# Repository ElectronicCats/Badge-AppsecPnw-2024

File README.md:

# Badge pnwCON 2024

## Getting started

1. Connect Badge via USB to your computer.
2. Open the serial port indicated for the badge on your computer through a program such as Arduino IDE, Putty or Screen at 115200 bauds.
3. The badge text should appear in the terminal.

## Tecnologia

- ESP32C6
- LEDs
- USB

## Gratitude
Do you want to say thank you? Tag these companies on social networks and show them your badge, thanks to them it is possible

- [WebSEC](https://www.websec.ca)
- [ElectronicCats](https://electroniccats.com/)

## License

Electronic Cats invests time and resources providing this open source design, please support Electronic Cats and open-source hardware by purchasing products from Electronic Cats!

Designed by Electronic Cats.

Hardware released under an CERN Open Hardware Licence v1.2. See the LICENSE_HARDWARE file for more information.

Electronic Cats is a registered trademark, please do not use if you sell these PCBs.

May 2024

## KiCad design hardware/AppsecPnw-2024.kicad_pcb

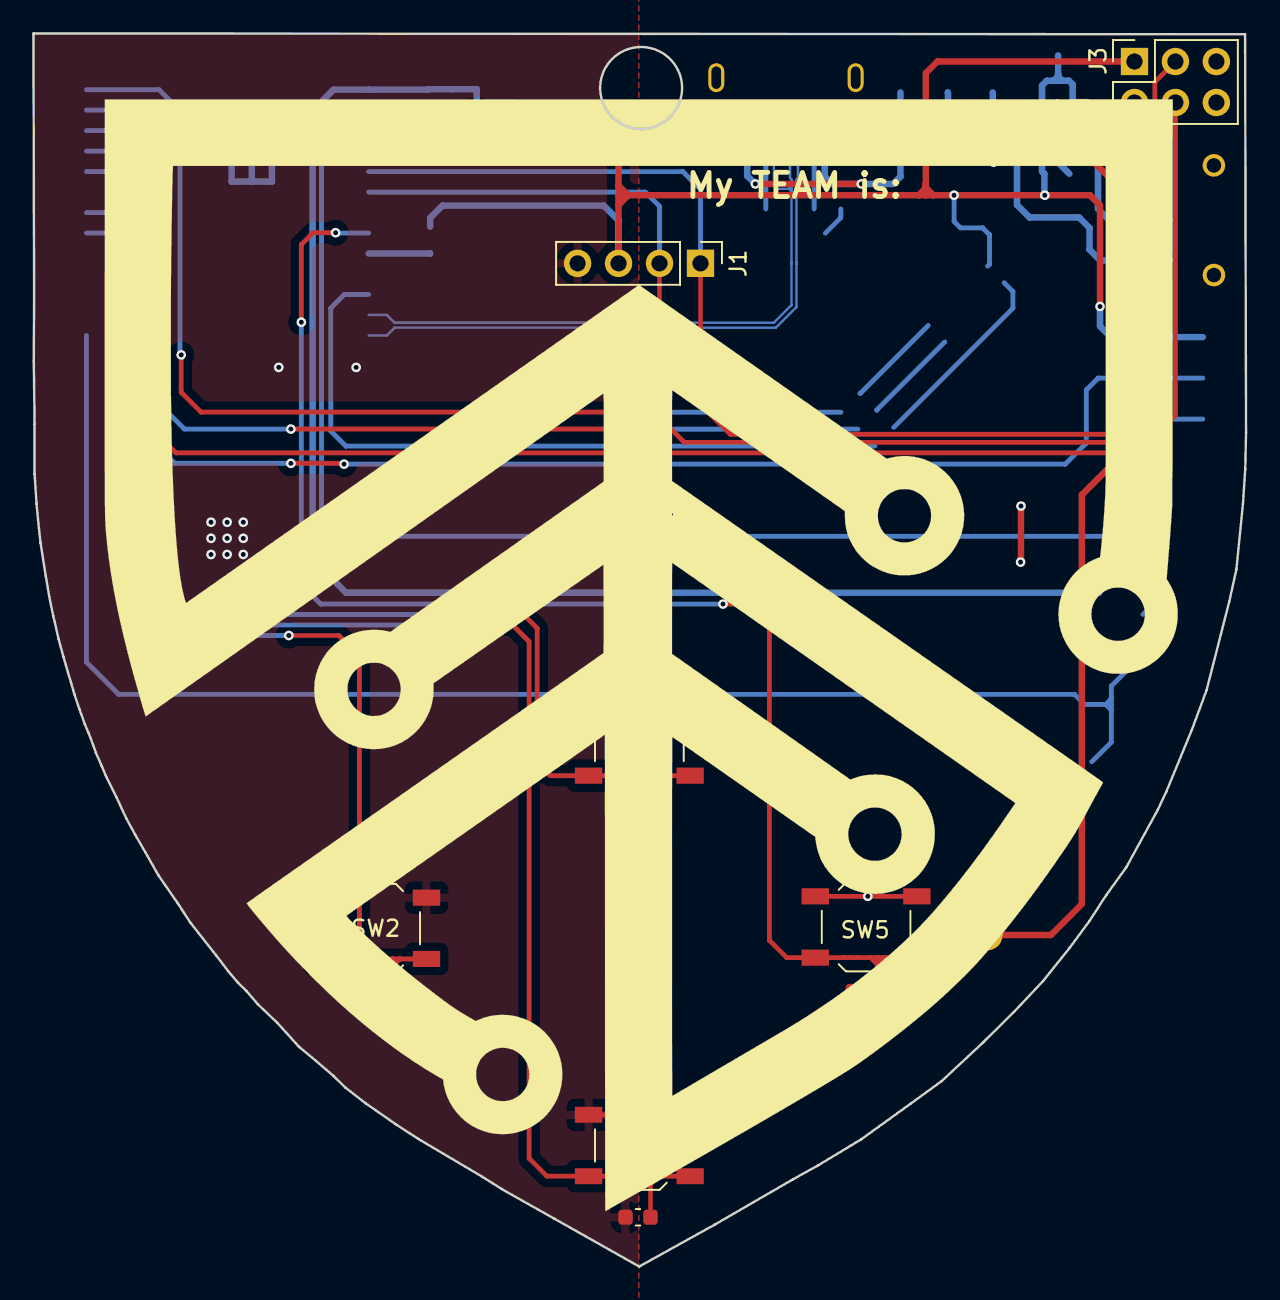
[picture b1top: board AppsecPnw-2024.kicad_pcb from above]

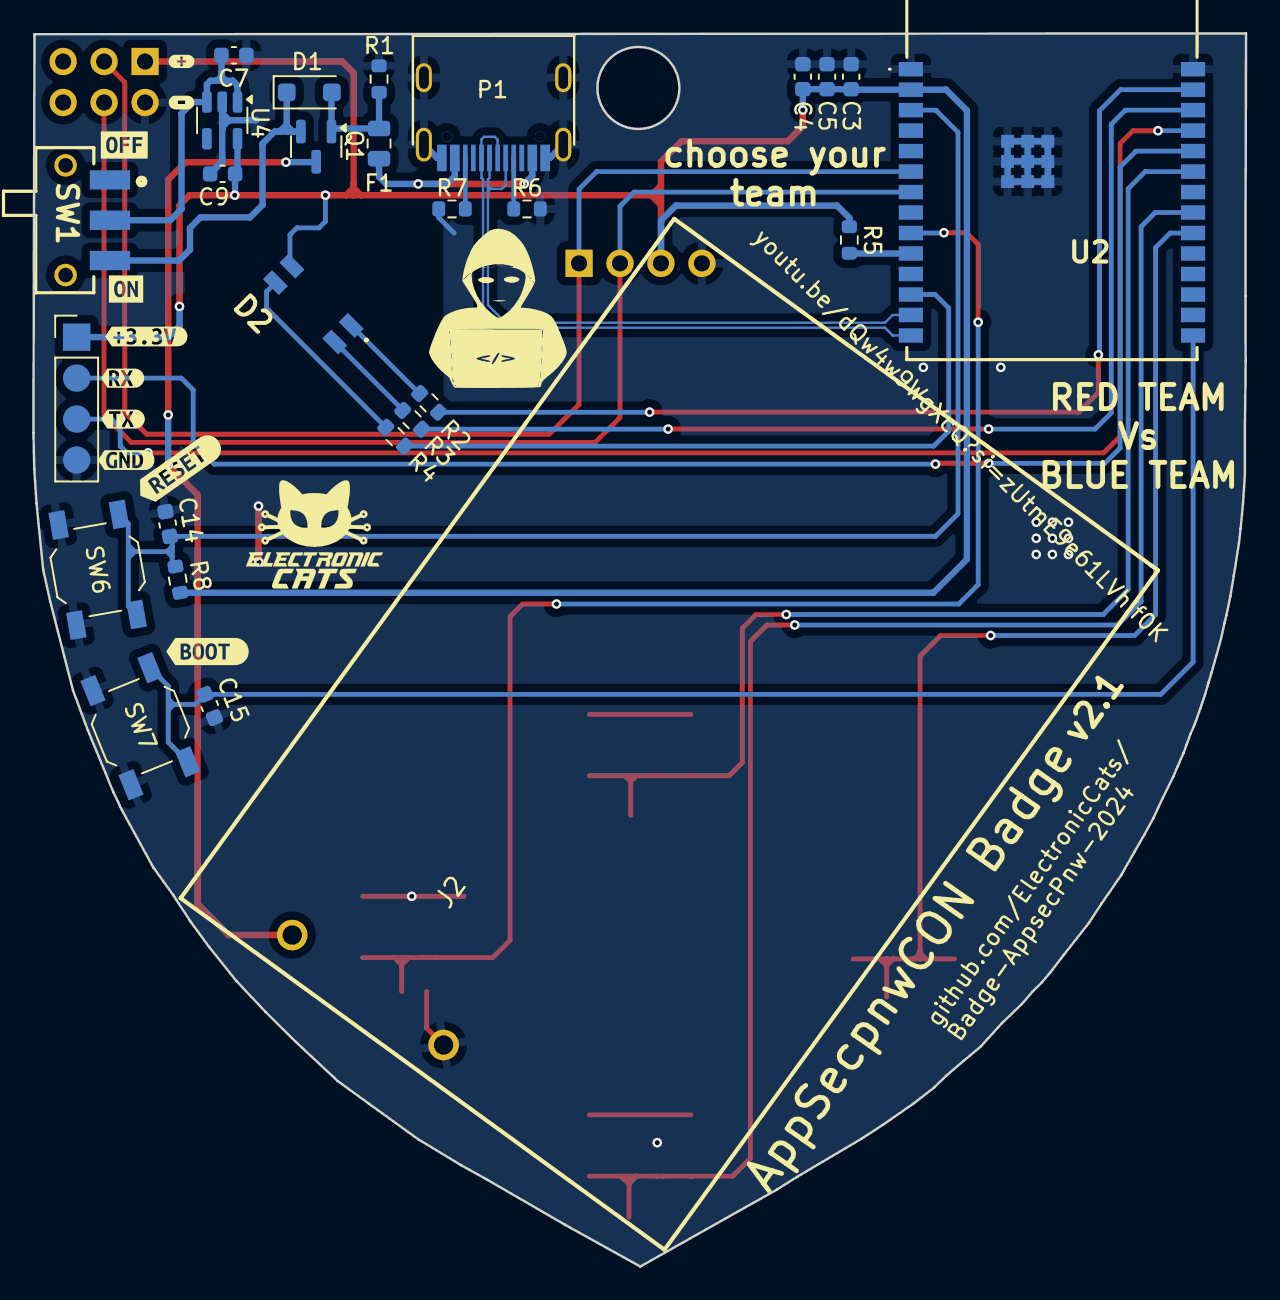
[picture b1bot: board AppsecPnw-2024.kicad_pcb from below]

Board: 2 copper layers, 75.2 x 76.5 mm, 48 parts (37 on the bottom side), 28 nets.

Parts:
C3: 1uF; C_0603_1608Metric
C4, C5, C7, C9: 10uF; C_0603_1608Metric
C10, C11, C12, C13, C14, C15: .1uF; C_0603_1608Metric
D1: MBR120; D_SOD-123F
D2: LED_RABG; AAA3528SURKCGKC09
F1: 1A; Fuse_0805_2012Metric
J1: OLED; Display OLED 128 x32
J2: Battery; BAT-TH_BH-AAA-A1AJ024
J3: Conn_02x03_Odd_Even; PinSocket_2x03_P2.54mm_Vertical
J5: UART; PinHeader_1x04_P2.54mm_Vertical
P1: USB_C_Plug_USB2.0; C393939
Q1: DMG3415U-7; SOT-23
R1: 100K; R_0603_1608Metric
R2, R3, R4: 330; R_0603_1608Metric
R5: 3.3K; R_0603_1608Metric
R6, R7: 5k1; R_0603_1608Metric
R8: 10K; R_0603_1608Metric
Ref**: Val**; Badge pnwcon
SW1: ON; JS102011SAQN
SW2: LEFT; SW_SPST_TL3342
SW3: DOWN; SW_SPST_TL3342
SW4: UP; SW_SPST_TL3342
SW5: RIGTH; SW_SPST_TL3342
SW6: RESET; SW_SPST_TL3342
SW7: BOOT; SW_SPST_TL3342
U2: ESP32-C6-WROOM-1-N4; ESP32C6WROOM1N4
U4: AP2112K-3.3; SOT-23-5
kibuzzard-660EECB7: G***; kibuzzard-660EECB7
kibuzzard-660EEDFA: G***; kibuzzard-660EEDFA
kibuzzard-663AC028: G***; kibuzzard-663AC028
kibuzzard-663AC038: G***; kibuzzard-663AC038
kibuzzard-663AC049: G***; kibuzzard-663AC049
kibuzzard-663AC054: G***; kibuzzard-663AC054
kibuzzard-6616FF4C: G***; kibuzzard-6616FF4C
kibuzzard-6616FF56: G***; kibuzzard-6616FF56
kibuzzard-6617003A: G***; kibuzzard-6617003A
kibuzzard-66170030: G***; kibuzzard-66170030

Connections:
+3V3: C3.1, C4.1, C5.1, C9.1, D2.2 (A), J1.3, J3.1, J5.1, R5.1, R8.2, U2.2 (3V3), U4.5 (VOUT)
+BATT: J2.2, Q1.3 (D)
/BACK: C10.2, SW2.2, U2.20 (IO22)
/BLUE: R4.1, U2.12 (IO11)
/BOOT: C15.2, SW7.2, U2.15 (IO9)
/D+: P1.A6 (D+), U2.14 (IO13)
/D-: P1.A7 (D-), U2.13 (IO12)
/DOWN: C11.2, SW3.2, U2.21 (IO23)
/EN: C14.2, R8.1, SW6.2, U2.3 (EN)
/GREEN: R3.1, U2.26 (IO3)
/IO8: R5.2, U2.10 (IO8)
/RED: R2.1, U2.27 (IO2)
/RX: J5.2, U2.24 (RXD0)
/SCL: J1.2, J3.4, U2.7 (IO7)
/SDA: J1.1, J3.3, U2.6 (IO6)
/SELECT: C13.2, SW5.2, U2.9 (IO1)
/TX: J5.3, U2.25 (TXD0)
/UP: C12.2, SW4.2, U2.23 (IO15)
GND: C3.2, C4.2, C5.2, C7.2, C9.2, C10.1, C11.1, C12.1, C13.1, C14.1, C15.1, J1.4, J2.1, J3.2, J5.4, P1.A1 (GND), P1.S1 (SHIELD), R1.2, R6.1, R7.1, SW2.1, SW3.1, SW4.1, SW5.1, SW6.1, SW7.1, U2.1 (GND_1), U2.28 (GND_2), U2.29 (GND_3), U2.30 (GND_4), U2.31 (GND_5), U2.32 (GND_6), U2.33 (GND_7), U2.34 (GND_8), U2.35 (GND_9), U2.36 (GND_10), U2.37 (GND_11), U4.2 (GND)
unnamed: D1.1 (K), Q1.2 (S), SW1.3 (A)
unnamed: D2.3 (BK), R4.2
unnamed: D2.4 (GK), R3.2
unnamed: D2.1 (RK), R2.2
unnamed: F1.1, P1.A4 (VBUS)
unnamed: P1.A5 (CC), R6.2
unnamed: P1.B5 (VCONN), R7.2
unnamed: C7.1, SW1.2 (B), U4.1 (VIN), U4.3 (EN)
VBUS: D1.2 (A), F1.2, Q1.1 (G), R1.1

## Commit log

2024-03-27 feat(hw): init schematic
2024-03-28 feat(Hw) Init PCB
2024-04-02 feat(Hw) Update schematic and floorplan
2024-04-03 feat(Hw) Update schematic
2024-04-04 feat(main) : Engine for Red team
    - OLED Driver ssd1306
    - Keyboard handle
    - BLE pairing
    - OWASP Profiles
    - Game Engine profile selection
2024-04-04 feat(Hw): Update schematic and init route
2024-04-04 feat(hw):add logos
2024-04-04 feat(engine) : Show OWASP Attacks
    - Show OWASP Attacks
2024-04-04 feat(Hw): Update labels
2024-04-04 feat(engine): Send attack
    - Send the attack from the profile and wait to response
2024-04-04 feat(ble) : Recive response from the client
2024-04-07 feat(engine): BLUE - RED Interaction
    - Interaction between Blue and Red device
    - Show screens for battle init
2024-04-07 feat(engine): Fix BLE commands
    - Fix the data array to send the ble commands
2024-04-07 feat(engine): Select team
    - Select team screen
    - Select team logic
2024-04-10 feat(hw): lables rst and boot
2024-04-10 feat(hw): add labels on/off
2024-04-10 feat(Hw): Update BOM
2024-04-11 feat(hw): add tickness
2024-04-11 fix(Hw): Change F1
2024-04-11 fix(Hw): fix dimensions layers and delete duplicated PCB thickness note
2024-04-13 feat: Engine communication
    - BLE Communication and first game steps
2024-04-14 feat(engine): Finish Game
    - Game Finish with the winner
2024-04-18 feat: Refactor code
    - State machine for engine
    - Better screens
    - Change folder struct
    - Decrease memory size to 4M
2024-04-19 feat: Implement Trackers Sniffing
    - Add Trackers functionality (AirTag and Tile)
    - Multi trackers sniffing
    - Show modal like information about tracke
    - Exit application & game with doble click
    Note: Tile tracker need to test with others
2024-04-19 feat: Fix screen
    - Add ADV information
    - Correct some issues
    - Refactor scanner code
2024-04-20 feat: Fix clean code
    - Refactor some function
    - Clear comments
2024-04-21 feat: Implement Wifi Scanner
    - Wifi scanner for the attack
    - Screen animation
2024-04-22 feat: Implement Broadcast Packets
    - Send deauth frames
2024-04-22 feat: Implement attacks
    - Rouge AP attack
    - Combined attack
2024-04-22 feat: Implement combined attacks
    - Bugs correction
    - Test functionality
    - Clean and document code
    - Create attack screen
    - Create Wifi as component
2024-04-23 feat: Refactor BLE
    - Moving BLE service
2024-04-24 feat: Implement BT as lib
    - Bt_gattc (Client)
    - BT_gattc (Server)
    You can call and setup to reuse the code
2024-04-24 feat: Implement ble spam
2024-04-29 feat: Refactor BLE and WIFI
    - Create modules
2024-04-30 feat: Implement BT Spam
    - Send bt packets
    - List of devices to spam
    - Some fixes in the Wifi and trackers
2024-04-30 feat: Implement Zigbee Sniffer
    - Show in console the information about the packets
2024-04-30 feat: Implement delete task
    - Delete task from the sniffer
2024-04-30 feat: Fix bugs
    - Fix BLE game bugs
    - Fix menu scrolling items
2024-05-01 feat: Refactor
    - Correct bugs
    - Led status
2024-05-01 feat: Implement Led lib
2024-05-02 feat: Fix bugs
    - BLE client pair by filter board name and RSSI
    - LED corrections
    - Engine fix bugs
2024-05-02 feat: Implement captive portal
    - Raw portal with google template
2024-05-03 feat: Implement fake wifi AP
    - Thief the passwod
    - Mlti AP attack
2024-05-03 feat: Implement Captive Portal
    - Google creds
    - Wifi password (Only Iphone)
2024-05-07 feat: Implement random options
    - Fix bugs
2024-05-07 feat:Update README.md
2024-05-07 fix(Hw): Change PCB and pull up resistor for boot added
2024-05-08 feat(): add labels
2024-05-08 feat: Implement device screens
    Screens:
    - Licence
    - Version
    - Credits
    - Legal
    Zigbee change channel with Up and Down button
2024-05-17 feat: Implement Michis Ranks
    - Rank based on Jedis and Sith
2024-05-17 feat: Implement Michi battle wars
    - Splash screen selector
    - Jedi and Sith michis
2024-05-20 feat: Update gitignore
    - Remove build folders and development folders
2024-05-20 feat: Merge conflicts
    - Change merge conflicts
2024-05-22 fix: conflicting types for zigbee_screens_display_scanning_text
2024-05-28 feat: Fix modules
    - Add long press exit in apps modules
    - Game dual badge
    - Game pairing exit
2024-05-28 feat: Fix merge conflicts
2024-05-29 feat: Fix bug
    - Change leds library
    - Solve I2C problem with wifi
2024-06-19 feat: Create LICENSE_HARDWARE
2024-06-19 Create LICENSE
2024-06-19 feat: Update firmware docs
